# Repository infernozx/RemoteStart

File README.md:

# RemoteStart
This project is for a remote start for a 2005 Dodge Ram 1500, with a 5.7L V8.

It's an attempt to design a low-cost remote start based off the arduino based "digispark" hardware.

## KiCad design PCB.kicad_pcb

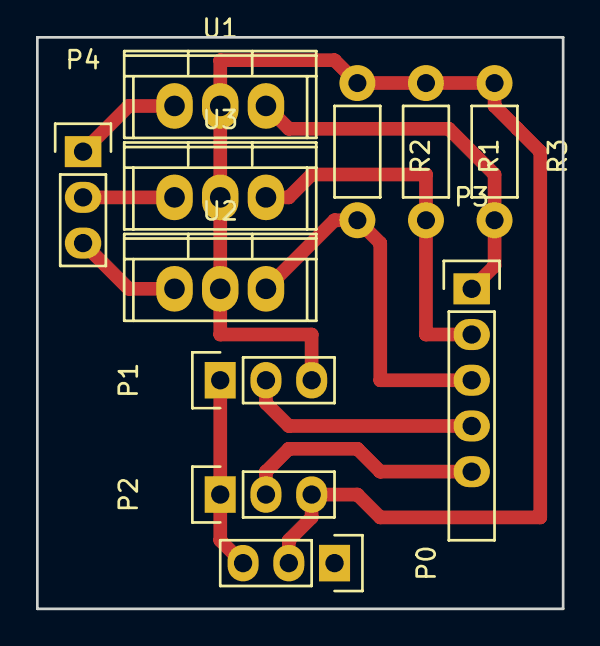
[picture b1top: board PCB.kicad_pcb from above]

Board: 2 copper layers, 29.2 x 31.8 mm, 11 parts (0 on the bottom side), 10 nets.

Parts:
P0: Power; Pin_Header_Straight_1x03
P1: StarterRelay; Pin_Header_Straight_1x03
P2: IgnitionRelay; Pin_Header_Straight_1x03
P3: DigisparkHeader; Pin_Header_Straight_1x06
P4: SensorInput; Pin_Header_Straight_1x03
R1, R2, R3: R; Resistor_Horizontal_RM7mm
U1, U2, U3: LM7805CT; TO-220

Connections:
unnamed: P0.2, P1.3, P2.3, R1.1, R2.1, R3.1, U1.2, U2.2, U3.2
unnamed: P0.3, P1.1, P2.1
unnamed: P1.2, P3.4
unnamed: P2.2, P3.5
unnamed: P3.1, R3.2, U1.3
unnamed: P3.2, R1.2, U3.3
unnamed: P3.3, R2.2, U2.3
unnamed: P4.1, U1.1
unnamed: P4.2, U3.1
unnamed: P4.3, U2.1

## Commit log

2017-01-09 Updates to the readme file.
2017-01-09 main file for the digispark
2017-01-10 printable kicad PCB layout file
    This is the PCB file, produced with KiCAD.
2017-01-10 PCB Schematic File
    PCB Schematic file created with KiCAD. Components list included.
